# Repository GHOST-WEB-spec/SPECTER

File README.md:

# ⚡ SPECTER

A handheld ESP32-based cybersecurity research tool running JINX OS. Built from scratch — custom firmware, custom PCB, custom 3D printed enclosure.

## ✨ Features

**📡 WiFi**
- Network scanner with OUI vendor lookup and threat assessment
- Probe request sniffer
- Evil Twin access point with captive portal credential capture
- KARMA attack — automatically impersonates known networks

**🔴 IR**
- TV-B-Gone (26 codes, all major brands)
- IR blaster with capture and replay
- IR self-test

**📶 BLE**
- Scanner with Apple device detection
- Apple BLE proximity spam (6 payloads)

**🔜 Coming Soon**
- CC1101 sub-GHz scanner and replay
- NFC read/write/clone
- RFID read/clone
- BadUSB payloads
- Deauth and beacon flood

## 🔧 Hardware

- ESP32-WROVER on Freenove extension board
- 2.8" ILI9341 TFT touchscreen (240x320)
- VS1838B IR receiver + TSAL6400 IR LEDs
- CC1101 x2 (sub-GHz radios)
- PN532 NFC module
- RDM6300 RFID module
- LiPo 1000mAh + TP4056 charging
- Custom KiCad PCB — ordered from JLCPCB
- 3D printed enclosure — Fusion 360

## 🚀 Status

Firmware working. PCB designed and ready to order. Parts arriving shortly for final assembly.

## 🛠️ Build

Flash using Arduino IDE with ESP32 core v2.0.17. Partition scheme: Huge APP 3MB No OTA.

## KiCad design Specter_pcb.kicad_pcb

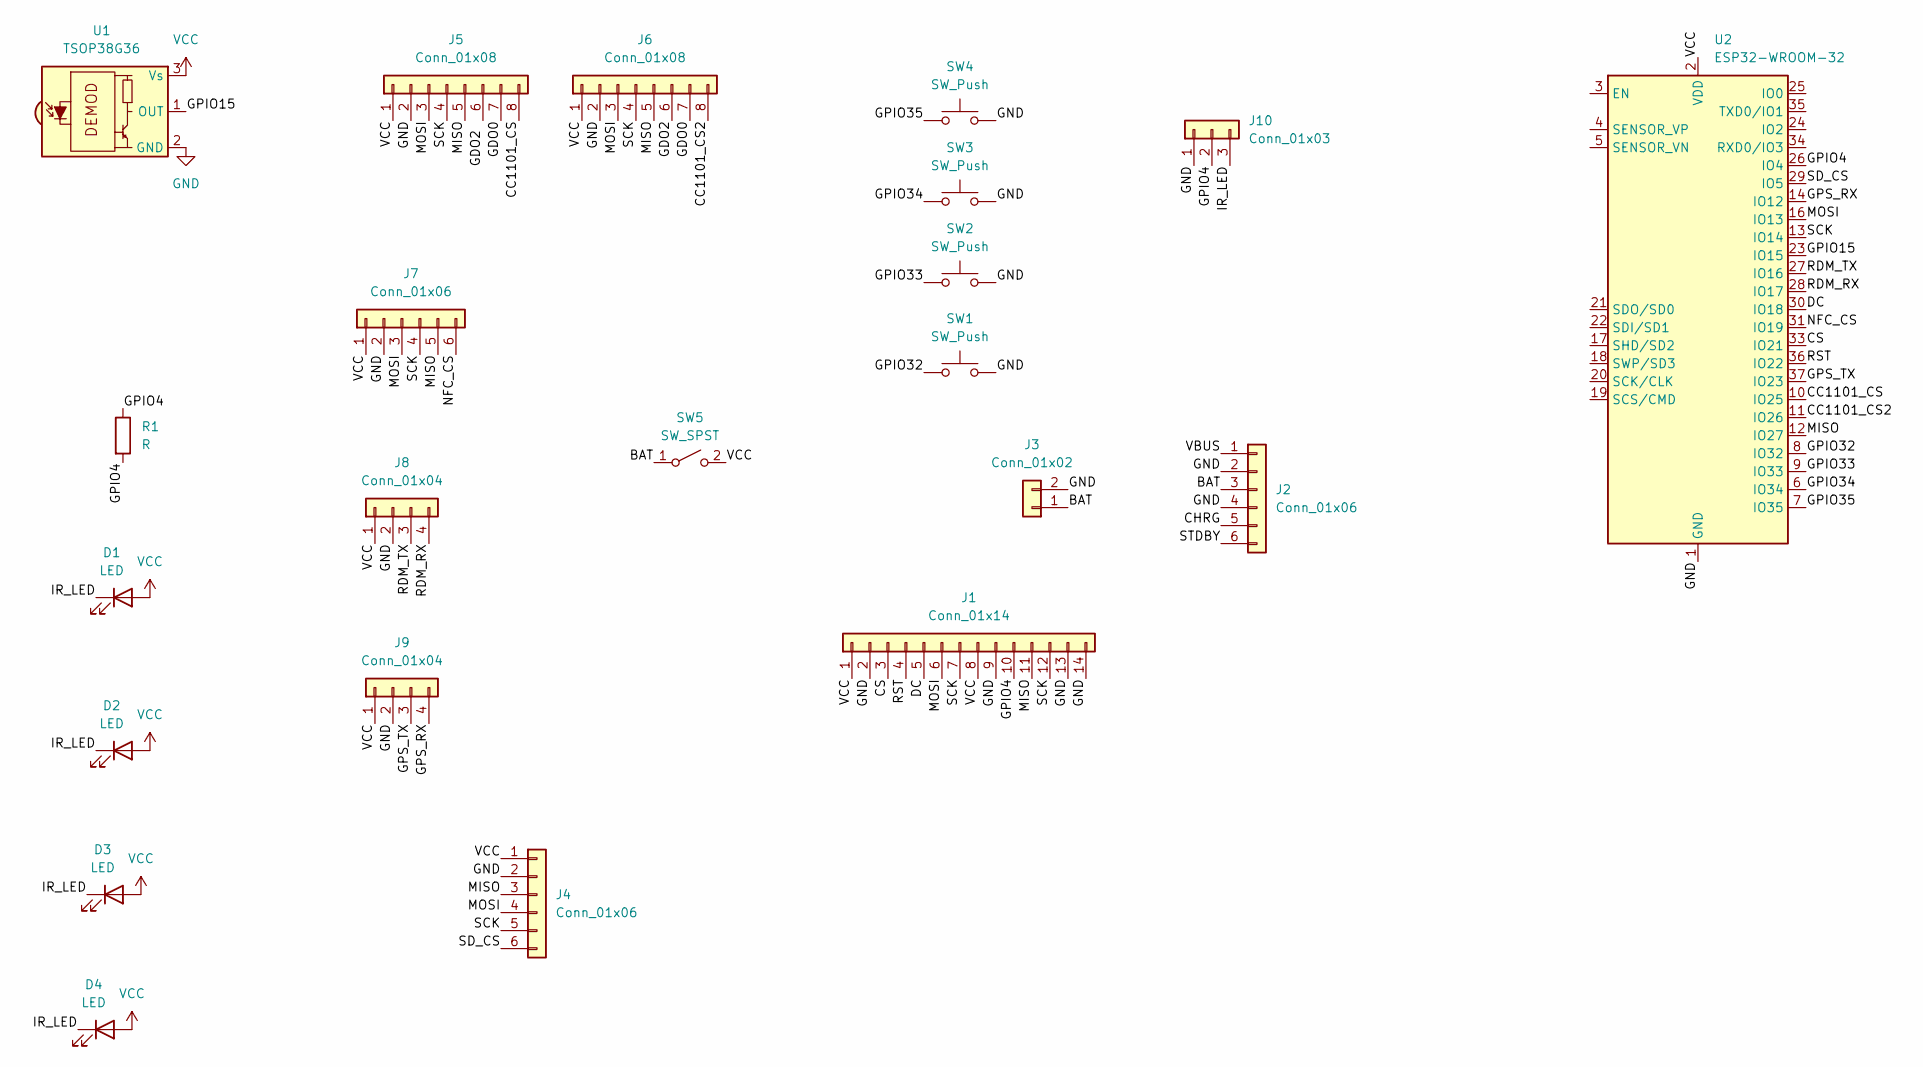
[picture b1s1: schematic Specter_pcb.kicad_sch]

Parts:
D1, D2, D3, D4: LED; LED_D5.0mm
J1: Conn_01x14; PinHeader_1x14_P2.54mm_Vertical
J2, J4, J7: Conn_01x06; PinHeader_1x06_P2.54mm_Vertical
J3: Conn_01x02; JST_PH_S2B-PH-K_1x02_P2.00mm_Horizontal
J5, J6: Conn_01x08; PinHeader_1x08_P2.54mm_Vertical
J8, J9: Conn_01x04; PinHeader_1x04_P2.54mm_Vertical
J10: Conn_01x03; PinHeader_1x03_P2.54mm_Vertical
R1: R; R_Axial_DIN0207_L6.3mm_D2.5mm_P7.62mm_Horizontal
SW1, SW2, SW3, SW4: SW_Push; SW_PUSH_6mm
SW5: SW_SPST; SW_NKK_BB15AH
U1: TSOP38G36; Vishay_MINICAST-3Pin
U2: ESP32-WROOM-32

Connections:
/BAT: J2.3, J3.1, SW5.1 (A)
/CC1101_CS: J5.8, U2.10 (IO25)
/CC1101_CS2: J6.8, U2.11 (IO26)
/CHRG: J2.5
/CS: J1.3, U2.33 (IO21)
/DC: J1.5, U2.30 (IO18)
/GDO0: J5.7, J6.7
/GDO2: J6.6
/GPIO4: J1.10, J10.2, R1.1, R1.2, U2.26 (IO4)
/GPIO15: U1.1 (OUT), U2.23 (IO15)
/GPIO32: SW1.1, U2.8 (IO32)
/GPIO33: SW2.1, U2.9 (IO33)
/GPIO34: SW3.1, U2.6 (IO34)
/GPIO35: SW4.1, U2.7 (IO35)
/GPS_RX: J9.4, U2.14 (IO12)
/GPS_TX: J9.3, U2.37 (IO23)
/IR_LED: D1.1 (K), D2.1 (K), D3.1 (K), D4.1 (K), J10.3
/MISO: J1.11, J4.3, J5.5, J6.5, J7.5, U2.12 (IO27)
/MOSI: J1.6, J4.4, J5.3, J6.3, J7.3, U2.16 (IO13)
/NFC_CS: J7.6, U2.31 (IO19)
/RDM_RX: J8.4, U2.28 (IO17)
/RDM_TX: J8.3, U2.27 (IO16)
/RST: J1.4, U2.36 (IO22)
/SCK: J1.7, J1.12, J4.5, J5.4, J6.4, J7.4, U2.13 (IO14)
/SD_CS: J4.6, U2.29 (IO5)
/STDBY: J2.6
/VBUS: J2.1
GND: J1.2, J1.9, J1.13, J1.14, J2.2, J2.4, J3.2, J4.2, J5.2, J6.2, J7.2, J8.2, J9.2, J10.1, SW1.2, SW2.2, SW3.2, SW4.2, U1.2 (GND), U2.1 (GND), U2.15 (GND), U2.38 (GND), U2.39 (GND)
VCC: D1.2 (A), D2.2 (A), D3.2 (A), D4.2 (A), J1.1, J1.8, J4.1, J5.1, J6.1, J7.1, J8.1, J9.1, SW5.2 (B), U1.3 (Vs), U2.2 (VDD)

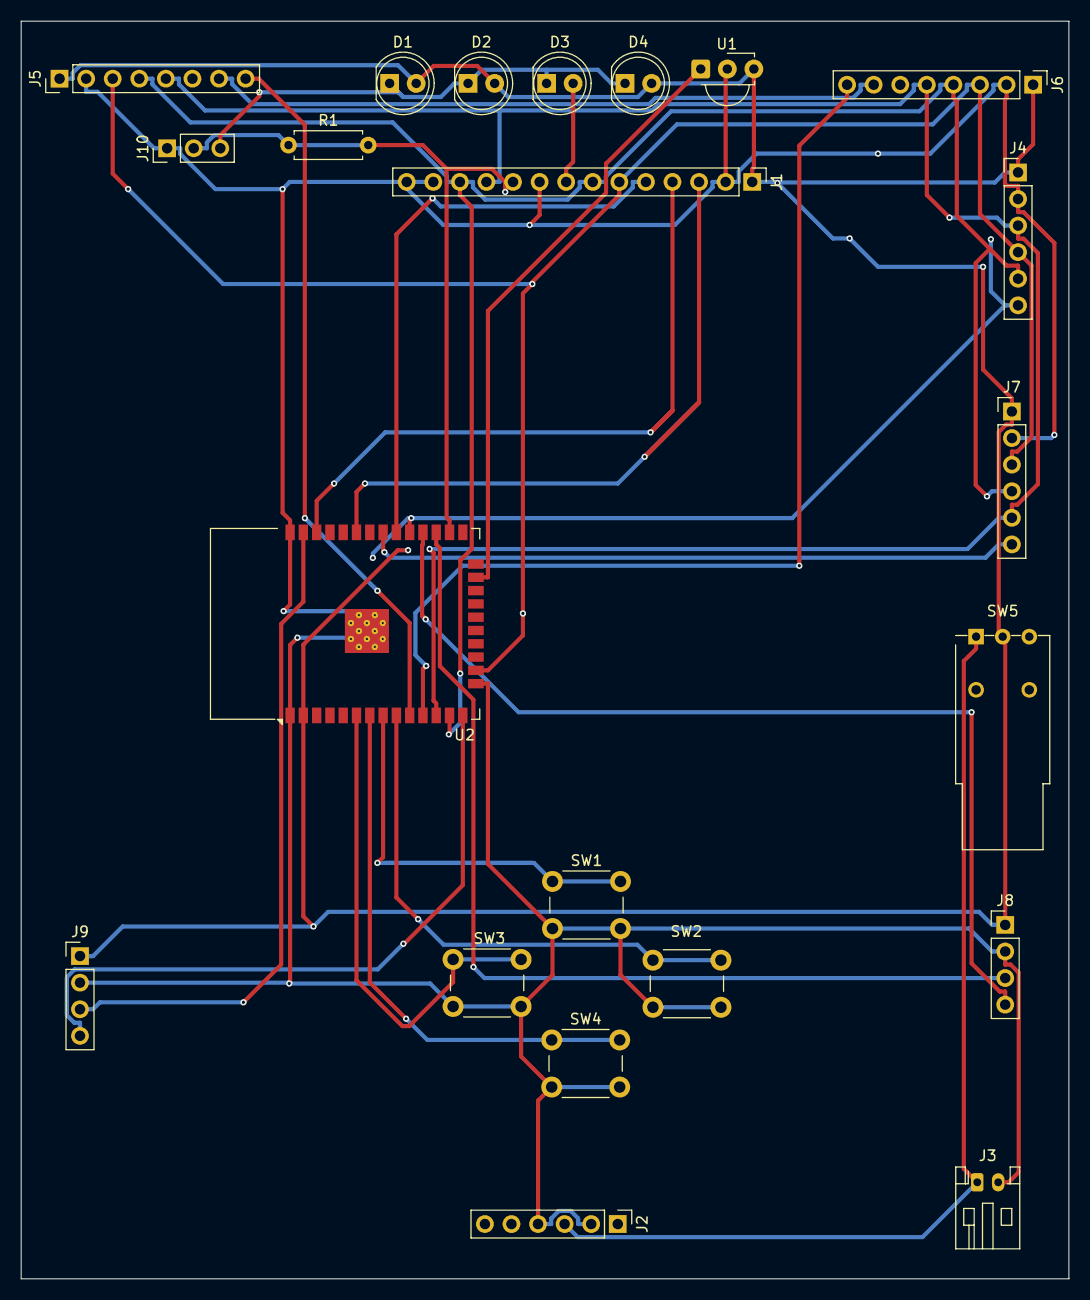
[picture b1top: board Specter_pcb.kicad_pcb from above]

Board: 2 copper layers, 100.1 x 120.2 mm, 22 parts (0 on the bottom side), 25 nets.

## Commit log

2026-03-30 JINX OS v9 - Evil Twin, KARMA, BLE spam, WiFi scanner
2026-03-30 Add JINX OS firmware
2026-03-30 Initialize README with project details and features
    Added detailed project description, features, hardware specifications, status, and build instructions for the SPECTER tool.
2026-03-30 Add .gitignore
